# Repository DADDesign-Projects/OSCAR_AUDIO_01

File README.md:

# OSCAR Audio Board - OSCAR_AUDIO_01

## 📋 Description

Dedicated electronic board implementing the audio section of the OSCAR effects pedal (https://github.com/DADDesign-Projects/OSCAR_P01A01). This board handles all digital and analog audio processing required for the pedal's operation.

## 🚀 Evolutions

### V2
- Modification of the output summing stage to restore phase alignment identical to the input signal

### V2.1 (PCB V2.2)
- Addition of a second relay to enable true hardware bypass

## 🛠️ Technical Specifications

### Audio Codec
- **PCM3060**: 24-bit stereo audio codec
- **ADC**: 2-channel, 24-bit resolution
- **DAC**: 2-channel, 24-bit resolution
- **Sampling Rate**: Up to 96 kHz

### Analog Dry Channel
- **PGA2310/PGA2311**: Stereo volume controller
- **Analog dry path** for unaffected signal
- **Independent wet/dry mix control**

### Power Supply
- **Isolated Power**: Separate analog and digital domains
- **Input Voltage**: 12V DC
- **Low Noise Regulation**: Multiple LDO regulators
- **Consumption**: < 150mA

## 🛠️ Design Tools
This project was entirely designed using **KiCad 10.0**, the open-source electronics design.

## 📜 License
This project is licensed under the **Apache License 2.0**.

# 📬 Contact
Feel free to contact me for any questions, feedback, improvement suggestions, or collaboration proposals related to the FORGE framework or the OSCAR hardware platform.
I am always open to discussion and community contributions (daddesign.projects@gmail.com).

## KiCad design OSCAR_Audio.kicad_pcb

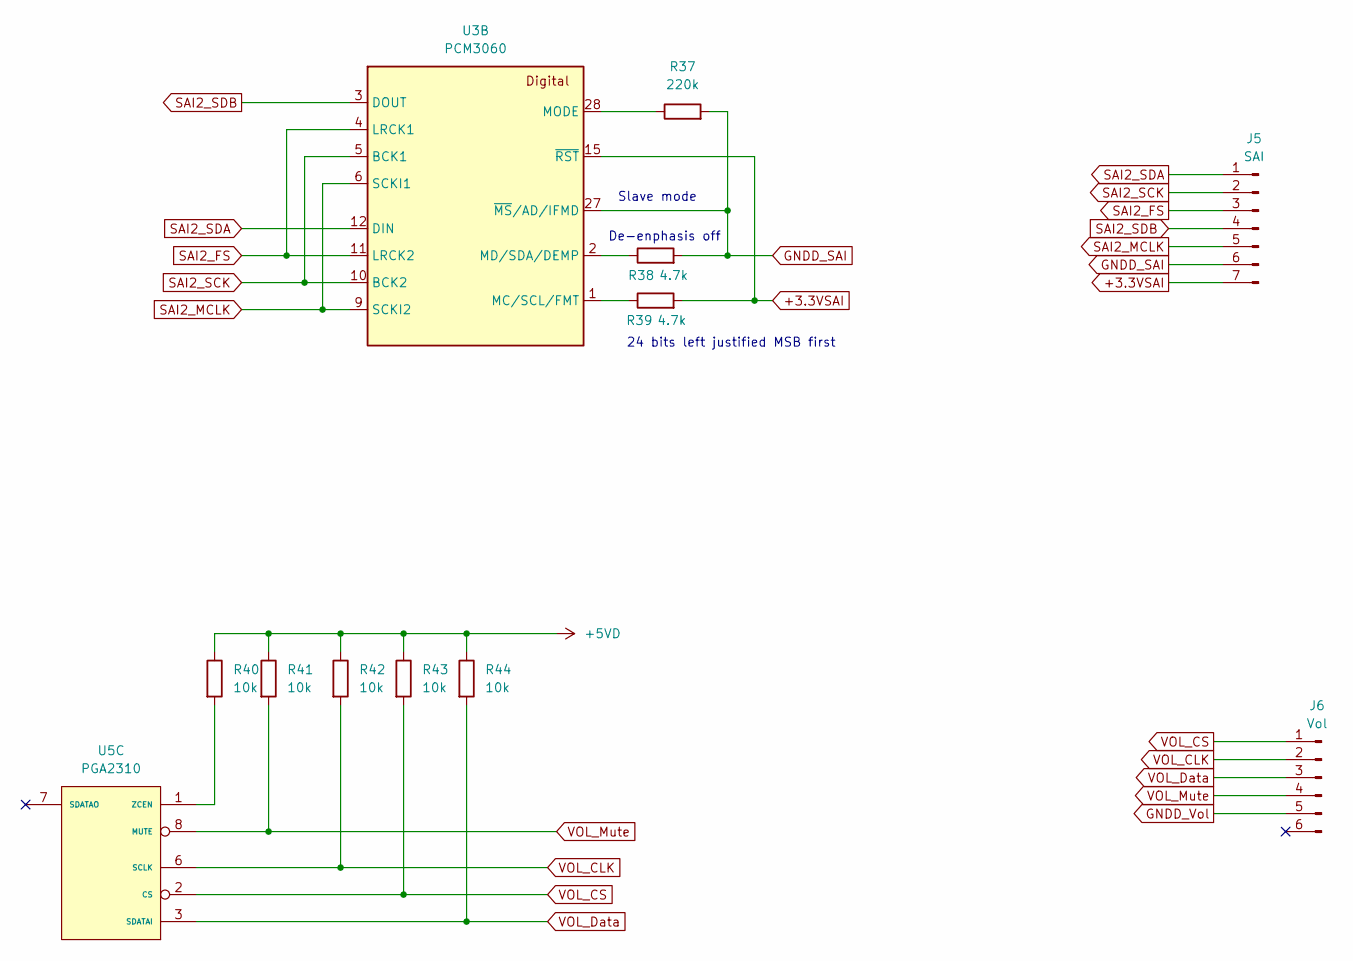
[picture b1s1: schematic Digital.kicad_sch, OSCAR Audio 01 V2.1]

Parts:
J5: SAI; PinHeader_1x07_P2.54mm_Vertical
J6: Vol; PinHeader_1x06_P2.54mm_Vertical
R37: 220k; R_1206_3216Metric_Pad1.30x1.75mm_HandSolder
R38, R39: 4.7k; R_1206_3216Metric_Pad1.30x1.75mm_HandSolder
R40, R41, R42, R43, R44: 10k; R_1206_3216Metric_Pad1.30x1.75mm_HandSolder
U3: PCM3060; TSSOP-28_4.4x9.7mm_P0.65mm
U5: PGA2310; SOIC-16W_7.5x10.3mm_P1.27mm

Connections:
+3.3VSAI: J5.7, R39.2, U3.15 (~RST); also elsewhere on the board
+5VD: R40.1, R41.1, R42.1, R43.1, R44.1; also elsewhere on the board
GNDD_SAI: J5.6, R37.2, R38.2, U3.27 (~MS/AD/IFMD); also elsewhere on the board
GNDD_Vol: J6.5; also elsewhere on the board
unnamed: R39.1, U3.1 (MC/SCL/FMT)
unnamed: R38.1, U3.2 (MD/SDA/DEMP)
unnamed: R37.1, U3.28 (MODE)
unnamed: R40.2, U5.1 (ZCEN)
SAI2_FS: J5.3, U3.4 (LRCK1), U3.11 (LRCK2)
SAI2_MCLK: J5.5, U3.6 (SCKI1), U3.9 (SCKI2)
SAI2_SCK: J5.2, U3.5 (BCK1), U3.10 (BCK2)
SAI2_SDA: J5.1, U3.12 (DIN)
SAI2_SDB: J5.4, U3.3 (DOUT)
VOL_CLK: J6.2, R42.2, U5.6 (SCLK)
VOL_CS: J6.1, R43.2, U5.2 (CS)
VOL_Data: J6.3, R44.2, U5.3 (SDATAI)
VOL_Mute: J6.4, R41.2, U5.8 (MUTE)

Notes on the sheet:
Slave mode
24 bits left justified MSB first
De-enphasis off

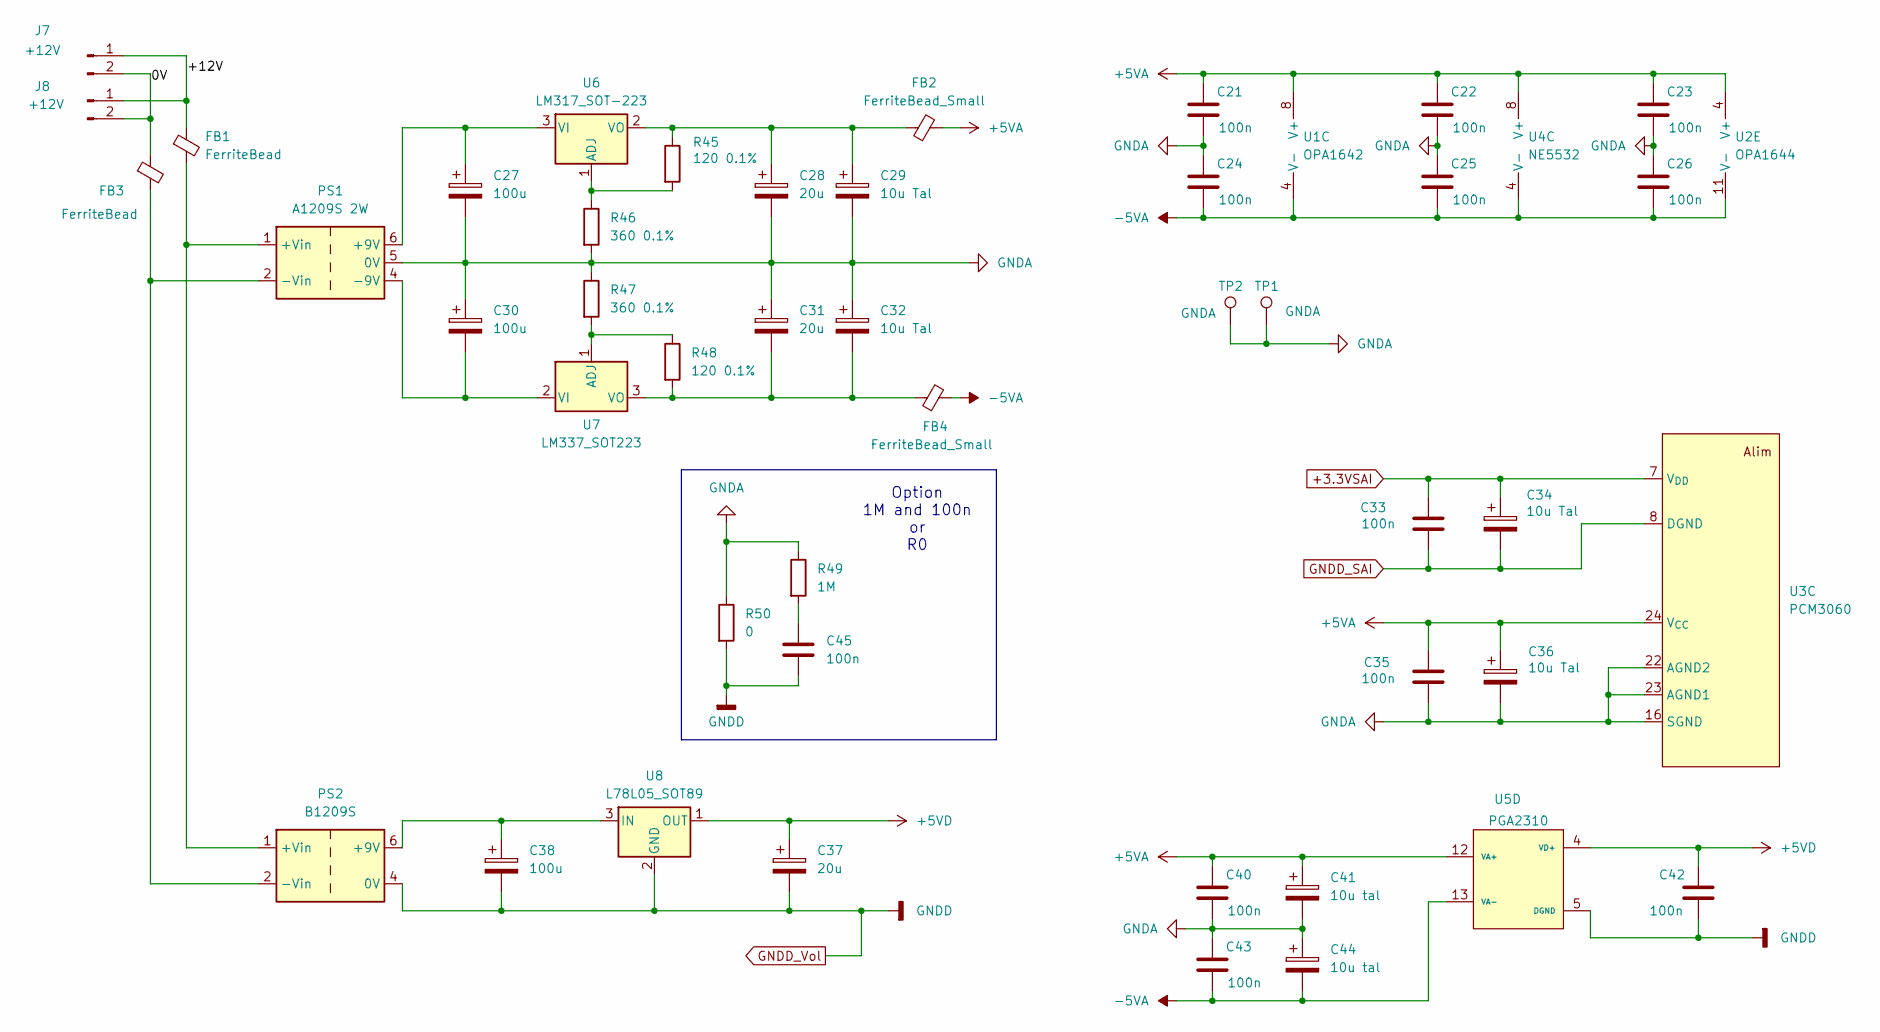
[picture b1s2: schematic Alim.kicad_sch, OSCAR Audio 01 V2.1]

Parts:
C21, C22, C23, C24, C25, C26, C33, C35, C40, C42, C43, C45: 100n; C_0805_2012Metric_Pad1.18x1.45mm_HandSolder
C27, C30, C38: 100u; CP_Elec_6.3x9.9_WM
C28, C31, C37: 20u; CP_Elec_5x5.4_WM
C29, C32, C34, C36: 10u Tal; CP_EIA-3528-21_Kemet-B_HandSolder
C41, C44: 10u tal; CP_EIA-3528-21_Kemet-B_HandSolder
FB1, FB3: FerriteBead; L_1206_3216Metric_Pad1.22x1.90mm_HandSolder
FB2, FB4: FerriteBead_Small; L_0805_2012Metric_Pad1.05x1.20mm_HandSolder
J7, J8: +12V; PinHeader_1x02_P2.54mm_Vertical
PS1: A1209S 2W; Converter_DCDC_TRACO_TBA2-xxxx_Dual_THT
PS2: B1209S; Converter_DCDC_TRACO_TBA2-xxxx_Single_THT
R45, R48: 120 0.1%; R_0805_2012Metric_Pad1.20x1.40mm_HandSolder
R46, R47: 360 0.1%; R_0805_2012Metric_Pad1.20x1.40mm_HandSolder
R49: 1M; R_1206_3216Metric_Pad1.30x1.75mm_HandSolder
R50: 0; R_1206_3216Metric_Pad1.30x1.75mm_HandSolder
TP1: GNDA; TestPoint_Pad_4.0x4.0mm
TP2: GNDA; Pin_D1.3mm_L11.0mm
U1: OPA1642; SOP-8_3.76x4.96mm_P1.27mm
U2: OPA1644; SOIC-14_3.9x8.7mm_P1.27mm
U3: PCM3060; TSSOP-28_4.4x9.7mm_P0.65mm
U4: NE5532; SOP-8_3.76x4.96mm_P1.27mm
U5: PGA2310; SOIC-16W_7.5x10.3mm_P1.27mm
U6: LM317_SOT-223; SOT-223-3_TabPin2
U7: LM337_SOT223; SOT-223-3_TabPin2
U8: L78L05_SOT89; SOT-89-3

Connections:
+3.3VSAI: C33.1, C34.1, U3.7 (V_{DD}); also elsewhere on the board
+5VA: C21.1, C22.1, C23.1, C35.1, C36.1, C40.1, C41.1, FB2.2, U1.8 (V+), U2.4 (V+), U3.24 (V_{CC}), U4.8 (V+), U5.12 (VA+)
+5VD: C37.1, C42.1, U5.4 (VD+), U8.1 (OUT); also elsewhere on the board
-5VA: C24.2, C25.2, C26.2, C43.2, C44.2, FB4.2, U1.4 (V-), U2.11 (V-), U4.4 (V-), U5.13 (VA-)
/Alim/0V: FB3.1, J7.2, J8.2
/Alim/+12V: FB1.1, J7.1, J8.1
GNDA: C21.2, C22.2, C23.2, C24.1, C25.1, C26.1, C27.2, C28.2, C29.2, C30.1, C31.1, C32.1, C35.2, C36.2, C40.2, C41.2, C43.1, C44.1, PS1.5 (0V), R46.2, R47.1, R49.1, R50.1, TP1.1 (1_1), TP2.1 (1_1), U3.16 (SGND), U3.22 (AGND2), U3.23 (AGND1); also elsewhere on the board
GNDD_SAI: C33.2, C34.2, U3.8 (DGND); also elsewhere on the board
GNDD_Vol: C37.2, C38.2, C42.2, C45.2, PS2.4 (0V), R50.2, U5.5 (DGND), U8.2 (GND); also elsewhere on the board
unnamed: C45.1, R49.2
unnamed: C27.1, PS1.6 (+9V), U6.3 (VI)
unnamed: FB1.2, PS1.1 (+Vin), PS2.1 (+Vin)
unnamed: C30.2, PS1.4 (-9V), U7.2 (VI)
unnamed: FB3.2, PS1.2 (-Vin), PS2.2 (-Vin)
unnamed: C38.1, PS2.6 (+9V), U8.3 (IN)
unnamed: R45.2, R46.1, U6.1 (ADJ)
unnamed: C28.1, C29.1, FB2.1, R45.1, U6.2 (VO)
unnamed: R47.2, R48.1, U7.1 (ADJ)
unnamed: C31.2, C32.2, FB4.1, R48.2, U7.3 (VO)

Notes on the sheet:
Option 1M and 100n or R0

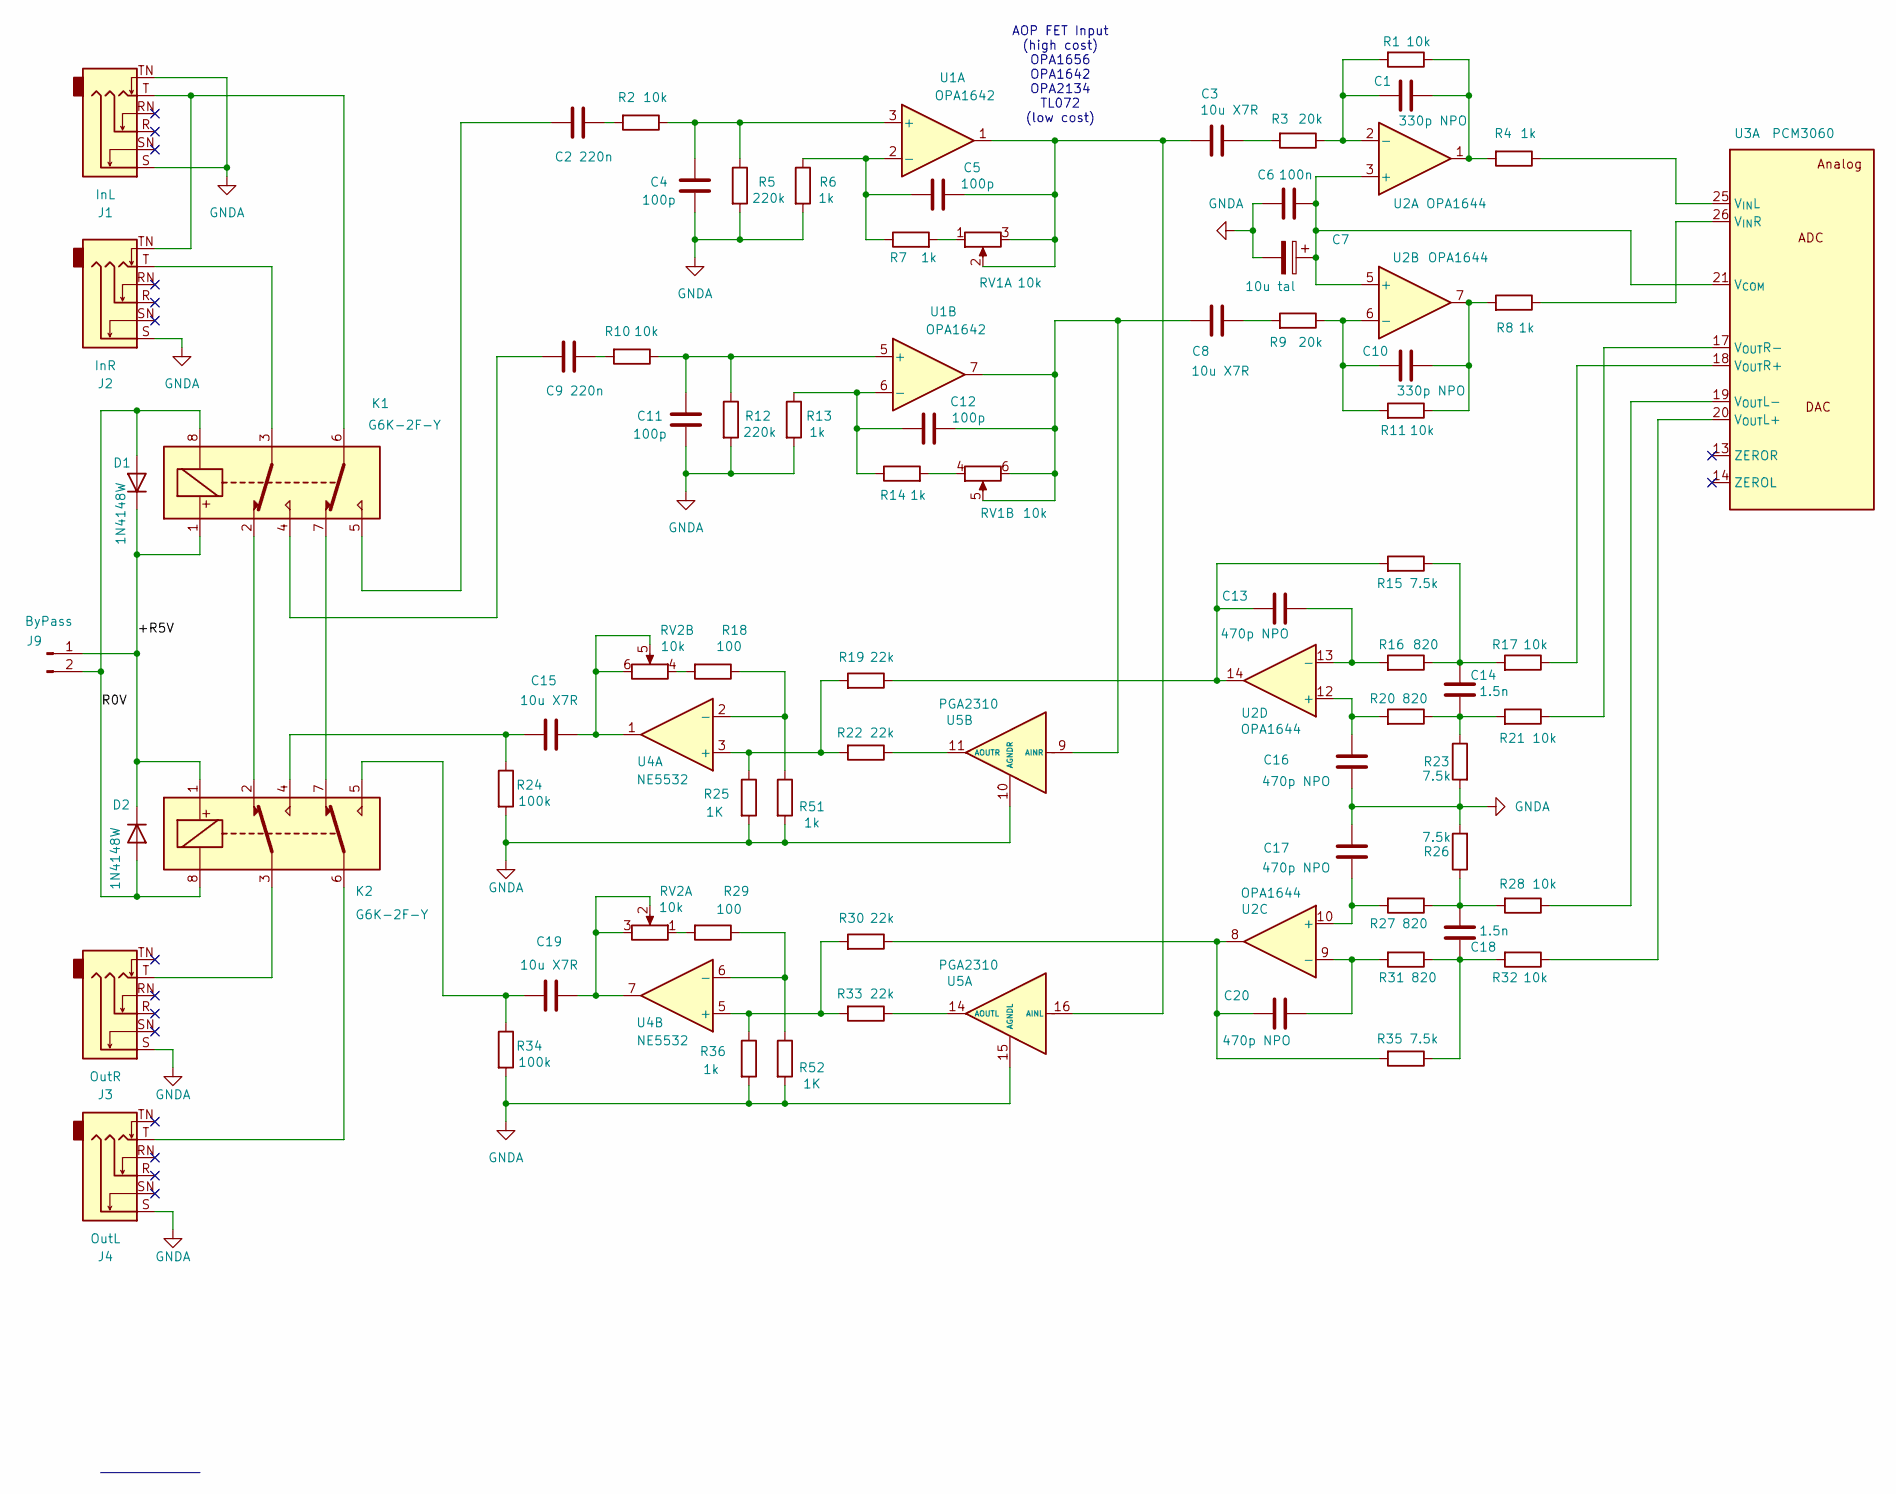
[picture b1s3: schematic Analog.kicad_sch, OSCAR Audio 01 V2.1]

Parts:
C1, C10: 330p NPO; C_0805_2012Metric_Pad1.18x1.45mm_HandSolder
C2, C9: 220n; C_1206_3216Metric_Pad1.33x1.80mm_HandSolder
C3, C8, C15, C19: 10u X7R; C_1206_3216Metric_Pad1.33x1.80mm_HandSolder
C4, C5, C11, C12: 100p; C_1206_3216Metric_Pad1.33x1.80mm_HandSolder
C6: 100n; C_0805_2012Metric_Pad1.18x1.45mm_HandSolder
C7: 10u tal; CP_EIA-3528-21_Kemet-B_HandSolder
C13, C16, C17, C20: 470p NPO; C_0805_2012Metric_Pad1.18x1.45mm_HandSolder
C14, C18: 1.5n; C_0805_2012Metric_Pad1.18x1.45mm_HandSolder
D1, D2: 1N4148W; D_SOD-123
J1: InL; Jack 6.25
J2: InR; Jack 6.25
J3: OutR; Jack 6.25
J4: OutL; Jack 6.25
J9: ByPass; PinHeader_1x02_P2.54mm_Vertical
K1, K2: G6K-2F-Y; Relay_DPDT_Omron_G6K-2F-Y
R1, R2, R10, R11, R17, R21, R28, R32: 10k; R_1206_3216Metric_Pad1.30x1.75mm_HandSolder
R3, R9: 20k; R_1206_3216Metric_Pad1.30x1.75mm_HandSolder
R4, R6, R7, R8, R13, R14, R36, R51: 1k; R_1206_3216Metric_Pad1.30x1.75mm_HandSolder
R5, R12: 220k; R_1206_3216Metric_Pad1.30x1.75mm_HandSolder
R15, R23, R26, R35: 7.5k; R_1206_3216Metric_Pad1.30x1.75mm_HandSolder
R16, R20, R27, R31: 820; R_1206_3216Metric_Pad1.30x1.75mm_HandSolder
R18, R29: 100; R_1206_3216Metric_Pad1.30x1.75mm_HandSolder
R19, R22, R30, R33: 22k; R_1206_3216Metric_Pad1.30x1.75mm_HandSolder
R24, R34: 100k; R_1206_3216Metric_Pad1.30x1.75mm_HandSolder
R25, R52: 1K; R_1206_3216Metric_Pad1.30x1.75mm_HandSolder
RV1, RV2: 10k; Potentioneter Double 1 ligne
U1: OPA1642; SOP-8_3.76x4.96mm_P1.27mm
U2: OPA1644; SOIC-14_3.9x8.7mm_P1.27mm
U3: PCM3060; TSSOP-28_4.4x9.7mm_P0.65mm
U4: NE5532; SOP-8_3.76x4.96mm_P1.27mm
U5: PGA2310; SOIC-16W_7.5x10.3mm_P1.27mm

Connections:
/Analog/+R5V: D1.1 (K), D2.1 (K), J9.1, K1.1, K2.1
/Analog/R0V: D1.2 (A), D2.2 (A), J9.2, K1.8, K2.8
GNDA: C4.1, C6.1, C7.2, C11.1, C16.1, C17.1, J1.S, J1.TN, J2.S, J3.S, J4.S, R5.2, R6.2, R12.2, R13.2, R23.2, R24.2, R25.2, R26.2, R34.2, R36.2, R51.2, R52.2, U5.10 (AGNDR), U5.15 (AGNDL); also elsewhere on the board
unnamed: C1.2, R1.1, R4.2, U2.1
unnamed: C2.1, K1.5
unnamed: C2.2, R2.2
unnamed: C3.2, R3.2
unnamed: C8.2, R9.2
unnamed: C9.1, K1.4
unnamed: C9.2, R10.2
unnamed: C10.2, R8.2, R11.1, U2.7
unnamed: C13.2, R15.2, R19.1, U2.14
unnamed: C14.1, R20.1, R21.2, R23.1
unnamed: C14.2, R15.1, R16.1, R17.2
unnamed: C15.1, K2.4, R24.1
unnamed: C15.2, RV2.5, RV2.6, U4.1
unnamed: C18.1, R26.1, R27.1, R28.2
unnamed: C18.2, R31.1, R32.2, R35.1
unnamed: C19.1, K2.5, R34.1
unnamed: C19.2, RV2.2, RV2.3, U4.7
unnamed: C20.2, R30.1, R35.2, U2.8
unnamed: J1.T, J2.TN, K1.6
unnamed: J2.T, K1.3
unnamed: J3.T, K2.3
unnamed: J4.T, K2.6
unnamed: K1.2, K2.2
unnamed: K1.7, K2.7
unnamed: R7.2, RV1.1
unnamed: R14.2, RV1.4
unnamed: R18.2, RV2.4
unnamed: R29.2, RV2.1
unnamed: C4.2, R2.1, R5.1, U1.3 (+)
unnamed: C5.1, R6.1, R7.1, U1.2 (-)
unnamed: C11.2, R10.1, R12.1, U1.5 (+)
unnamed: C12.1, R13.1, R14.1, U1.6 (-)
unnamed: C6.2, C7.1, U2.3 (+), U2.5 (+), U3.21 (V_{COM})
unnamed: C1.1, R1.2, R3.1, U2.2 (-)
unnamed: C10.1, R9.1, R11.2, U2.6 (-)
unnamed: C17.2, R27.2, U2.10 (+)
unnamed: C20.1, R31.2, U2.9 (-)
unnamed: C16.2, R20.2, U2.12 (+)
unnamed: C13.1, R16.2, U2.13 (-)
unnamed: R4.1, U3.25 (V_{IN}L)
unnamed: R8.1, U3.26 (V_{IN}R)
unnamed: R32.1, U3.20 (V_{OUT}L+)
unnamed: R28.1, U3.19 (V_{OUT}L-)
unnamed: R17.1, U3.18 (V_{OUT}R+)
unnamed: R21.1, U3.17 (V_{OUT}R-)
unnamed: R19.2, R22.2, R25.1, U4.3 (+)
unnamed: R18.1, R51.1, U4.2 (-)
unnamed: R30.2, R33.2, R36.1, U4.5 (+)
unnamed: R29.1, R52.1, U4.6 (-)
unnamed: C3.1, C5.2, RV1.2, RV1.3, U1.1, U5.16 (AINL)
unnamed: R33.1, U5.14 (AOUTL)
unnamed: C8.1, C12.2, RV1.5, RV1.6, U1.7, U5.9 (AINR)
unnamed: R22.1, U5.11 (AOUTR)

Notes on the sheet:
AOP FET Input (high cost) OPA1656 OPA1642 OPA2134 TL072 (low cost)

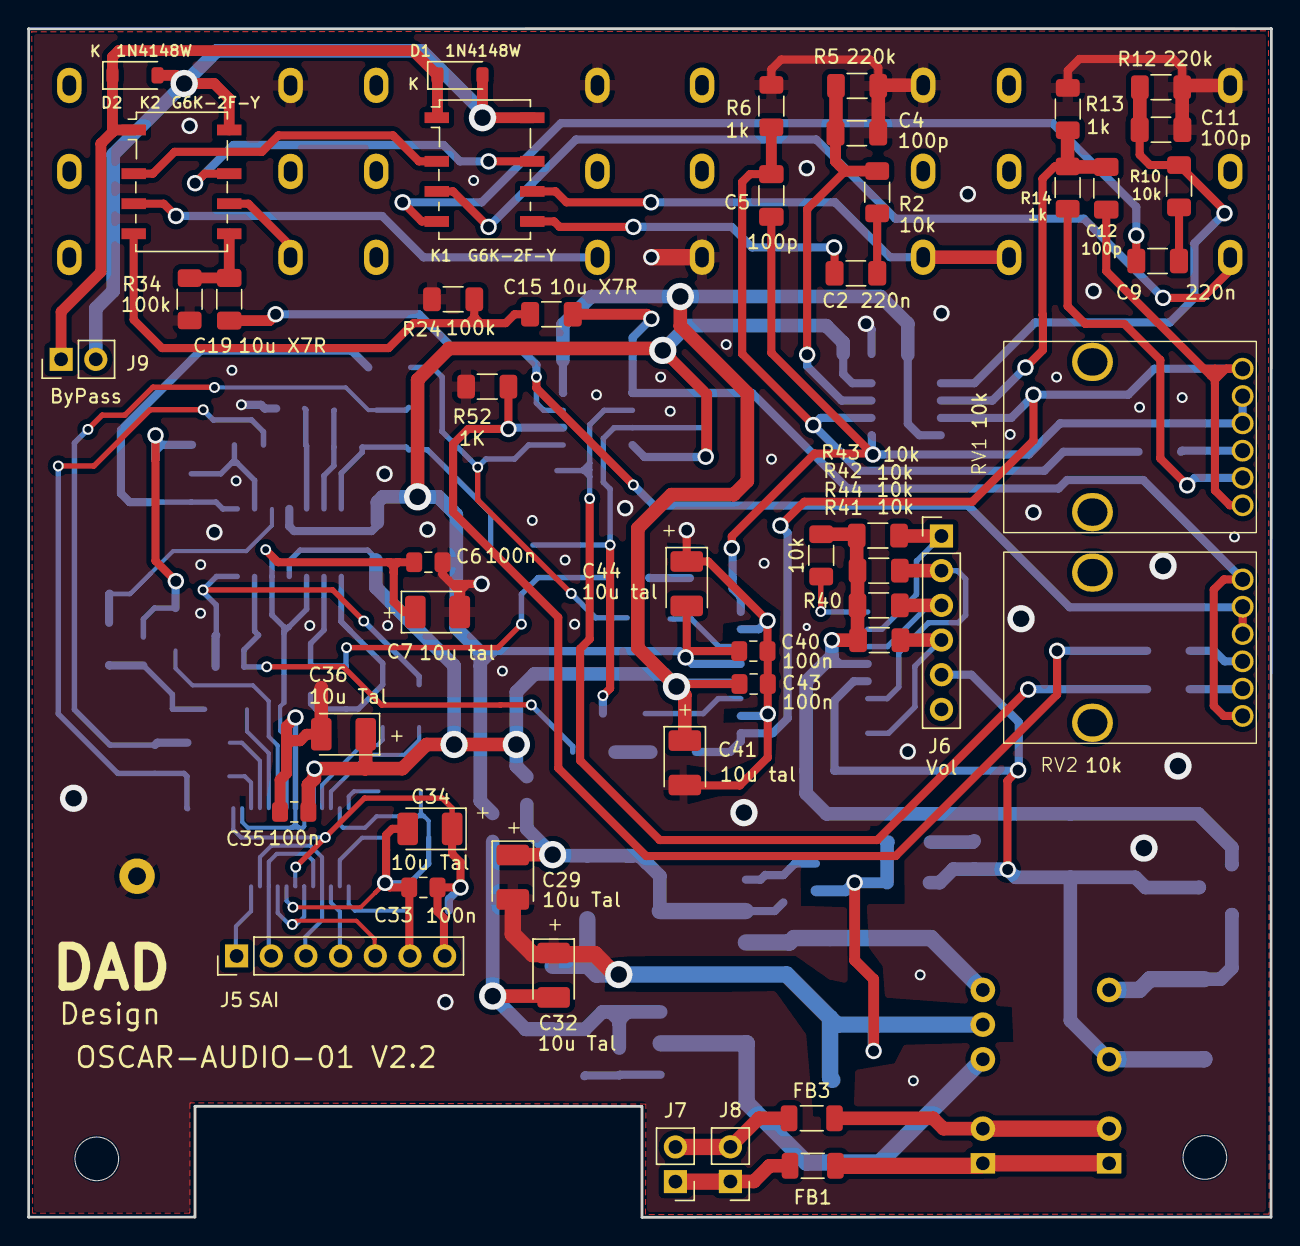
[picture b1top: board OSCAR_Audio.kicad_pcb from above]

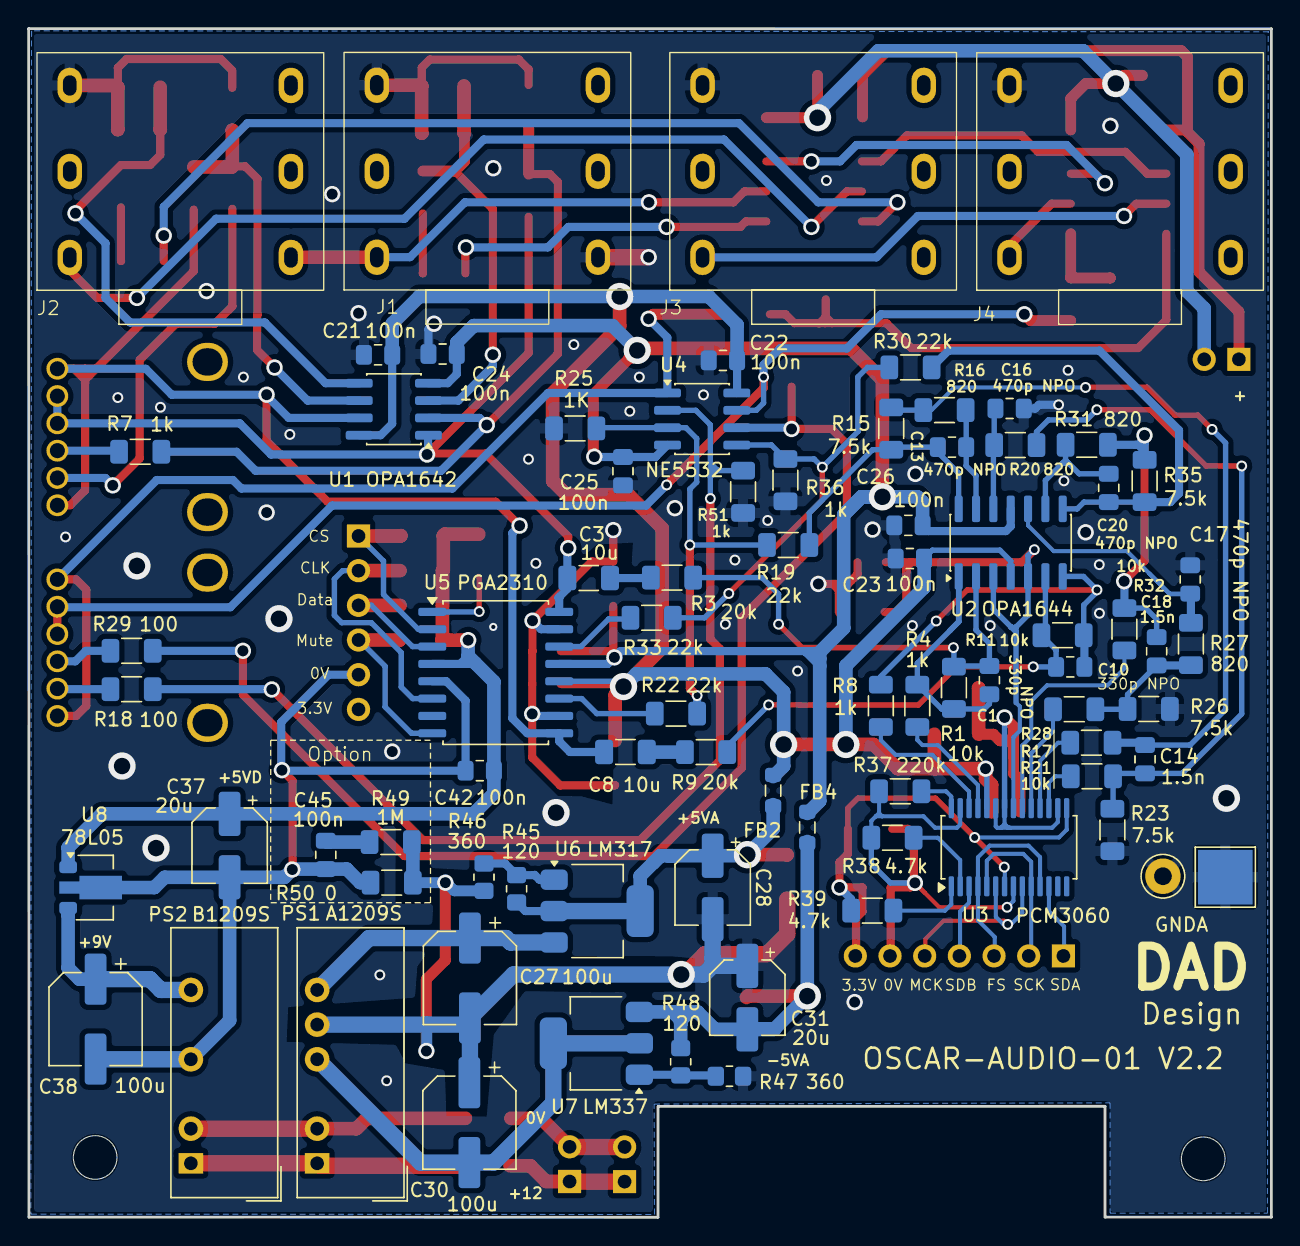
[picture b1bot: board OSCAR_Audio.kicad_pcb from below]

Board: 2 copper layers, 91.0 x 87.1 mm, 127 parts (79 on the bottom side), 87 nets.

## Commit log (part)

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2025-11-16 Update README with project details and specs
    Added detailed description and specifications for OSCAR Audio Board.
2025-11-16 Update README with KiCad badge and design tools info
    Added KiCad badge and design tools section to README.
2026-02-13 Fix typo OPA1612 -> OPA1642. Note: an OPA with FET inputs is necessary here.
    /!\ An OPA with FET inputs is necessary here.
2026-04-05 Invert output summing stage to maintain correct phase
2026-04-06 Define R25 and R36 to 1k

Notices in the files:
README.md:
License: Apache 2.0
